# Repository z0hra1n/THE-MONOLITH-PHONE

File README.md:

# MONOLITH

Ahh, i finally get to yap about it.
This is MONOLITH. a phone, a brick , a portable computer, but most importantly, a MONOLITH.
The reason im calling it a monolith cuz its literally gonna be built like a shiny MONOLITH. especially because its outer body is inteded to be made from aluminum which acts as a passive heat sink and looks pretty cool.The design was heavily inspired by Nothing and Apple.

The pcb is quite complicated, and the design is pretty human.It was not easy to make as i am only 15, this is my second pcb, the schematic itself was very hard.The pcb ws harder.I got help from reddit and tomachie.com with the schematic so it was pretty easy to disagnose.But, when it came to me m,aking the pcb, after i was done connecting everything, the drc gave 2000 violations.I was scared, but turns out most of those were easy fixable in one or two clicks.I also did not keep in mind the manufacturing constraints, so i fixed the values, and most of the errors were gone.I was pleased.

Finally, i made the enclosure very minimalist and functional.The back has a plastic went to let out the rf and wifi/bt signals.
the rear camera physically rotates to become the selfie camera.

The specs are pretty nuts.It has the radxa nx5 16 gb ram and 256 emms variant.An oled with 120hz refresh rate, and a batter of about 120000 mah.Im not sure itll last much without optimisation tho.

Yeah! i hope it overtakes apple!

| Purpose | Component / Item | Qty | Cost (USD) | Distributor | Part Number |
|---------|-------------------|----:|-----------:|------------|-------------|
| Decoupling | 10µF 25V X5R 0603 Capacitor | 10 | $1.46 | Digi-Key | GRM188R61E106MA73J |
| Bulk Decoupling | 22µF 16V 0603 Capacitor | 12 | $4.44 | Digi-Key | GMC10X5R226M16NTCT |
| Power Filtering | 1µF 25V X7R 0603 Capacitor | 10 | $0.52 | Digi-Key | TMK107B7105KA-T |
| Signal Filtering | 10nF 100V X7R Capacitor | 5 | $0.48 | Digi-Key | GCM188R72A103KA37D |
| Signal Filtering | 47nF 50V X7R Capacitor | 5 | $1.00 | Digi-Key | GCM188R71H473KA55D |
| Decoupling | 100nF 50V Y5V Capacitor | 5 | $0.48 | Digi-Key | CC0603ZRY5V9BB104 |
| Crystal Load | 18pF C0G Capacitor | 5 | $1.29 | Digi-Key | QSCP251Q180J1GV001T |
| Power Filtering | 4.7µF 25V X5R Capacitor | 5 | $1.15 | Digi-Key | GRM188R61E475KE11D |
| Pull-ups / General | 10kΩ 1% Resistor | 15 | $0.46 | Digi-Key | CRCW060310K0FKEA |
| Voltage Divider | 47kΩ 1% Resistor | 5 | $0.48 | Digi-Key | RC0603FR-0747KL |
| Feedback Divider | 255kΩ 1% Resistor | 5 | $0.48 | Digi-Key | ERJ-3EKF2553V |
| Feedback Divider | 180kΩ 5% Resistor | 5 | $0.48 | Digi-Key | RC0603JR-07180KL |
| Feedback Divider | 56kΩ 1% Resistor | 5 | $0.48 | Digi-Key | ERJ-3EKF5602V |
| Pull-ups | 2.2kΩ 1% Resistor | 10 | $0.24 | Digi-Key | RC0603FR-072K2L |
| USB Configuration | 5.1kΩ 1% Resistor | 5 | $0.53 | Digi-Key | RC0603FR-075K1L |
| Precision Divider | 29.8kΩ 0.1% Resistor | 5 | $0.53 | Digi-Key | RT0603BRD0729K8L |
| General Purpose | 12kΩ 1% Resistor | 5 | $0.48 | Digi-Key | RC0603FR-0712KL |
| Feedback Divider | 240kΩ 5% Resistor | 5 | $0.48 | Digi-Key | ERJ-3GEYJ244V |
| General Purpose | 1kΩ 1% Resistor | 5 | $0.48 | Digi-Key | CRCW06031K00FKEA |
| Compute Module Interface | 260-pin SODIMM Socket | 2 | $3.50 | Digi-Key | 2309407-1 |
| Display Interface | 22-pin FFC Connector | 2 | $4.91 | Digi-Key | FH12-22S-0.5SH(55) |
| Display Output | Micro HDMI Receptacle | 2 | $3.94 | Digi-Key | 0467651301 |
| USB Connectivity | USB Type-C Receptacle | 2 | $0.61 | Digi-Key | USB4970-00-A |
| Battery Charging | BQ25895 Li-Ion Charger IC | 2 | $6.42 | Digi-Key | BQ25895RTWR |
| Audio Output | SSM2518 Class-D Amplifier | 1 | $7.18 | Digi-Key | SSM2518CPZ |
| Input Protection | 6V TVS Diode | 2 | $0.92 | Digi-Key | SMAJ6.0CA |
| 5V Power Rail | TPS61088 10A Boost Converter | 2 | $5.24 | Digi-Key | TPS61088RHLR |
| USB Protection | USB ESD Protection IC | 5 | $5.64 | Digi-Key | TPD2EUSB30DRTR |
| RF Connection | U.FL (MHF1) Coax Cable | 1 | $2.04 | Digi-Key | CA-DKCA1-100L1-I0I0 |
| USB Expansion | USB2512B 2-Port USB Hub | 2 | $3.36 | Digi-Key | USB2512B-AEZG |
| Motion Sensing | BMI270 IMU | 1 | $4.04 | Digi-Key | BMI270 |
| Clock Source | 24MHz Crystal | 2 | $0.99 | Digi-Key | 535-10643-1 |
| User Input | Tactile Push Button | 5 | $1.82 | Digi-Key | SWT0005-015516SSAC |
| Power Stage | 2.2µH 15A Inductor | 2 | $2.81 | Digi-Key | MWSA1205S-2R2MT |
| Power Stage | 1µH 10A Inductor | 2 | $4.41 | Digi-Key | 74437349010 |
| 1.8V Rail | AP2112K 1.8V LDO | 2 | $0.52 | Digi-Key | AP2112K-1.8TRG1 |
| 3.3V Rail | TLV75533 3.3V LDO | 2 | $0.59 | Digi-Key | TLV75533PDQNR |
| Cellular Connectivity | LTE FPC Antenna | 1 | $2.81 | Digi-Key | AANI-FB-0173 |
| Display Cable | Micro HDMI to Mini HDMI Cable | 1 | $4.68 | Digi-Key | FIT0649 |
| USB Accessories | USB-A to Micro USB Cable | 2 | $3.02 | Digi-Key | DH-20M50055 |
| USB Accessories | USB-C to USB-C Cable | 1 | $4.46 | Digi-Key | 10165794-Z0100YBLF |
| Additional Decoupling | 100nF X7R Capacitor | 10 | $0.67 | Digi-Key | C0603C104K3RACTU |
| Thermal Management | Heat Sink Thermal Sticker | 1 | $1.43 | Digi-Key | 6308 |
| Assembly | Kapton Tape (10mm) | 1 | $2.78 | Digi-Key | KAPTON-TAPE10MM |
| Temperature Monitoring | 10kΩ NTC Thermistor | 2 | $1.88 | Digi-Key | B57861S0103F040 |
| Camera | 12MP IMX477P Camera Module | 1 | $59.99 | Arducam | B0517 |
| Miscellaneous | Batteries, BLE Module, Connectors | 4 | $290.47 | AliExpress | Various |
| PCB Manufacturing | PCB Fabrication + Engineering | 1 | $72.96 | PCB Fab | — |
| Portable Power | 20,000mAh Power Bank | 1 | $30.29 | Amazon | Duracell |
| Enclosure | CNC Aluminium Enclosure (Estimate) | 1 | $100.00 | Local Fabricator | — |
| **TOTAL** | | | **$649.81** | | |

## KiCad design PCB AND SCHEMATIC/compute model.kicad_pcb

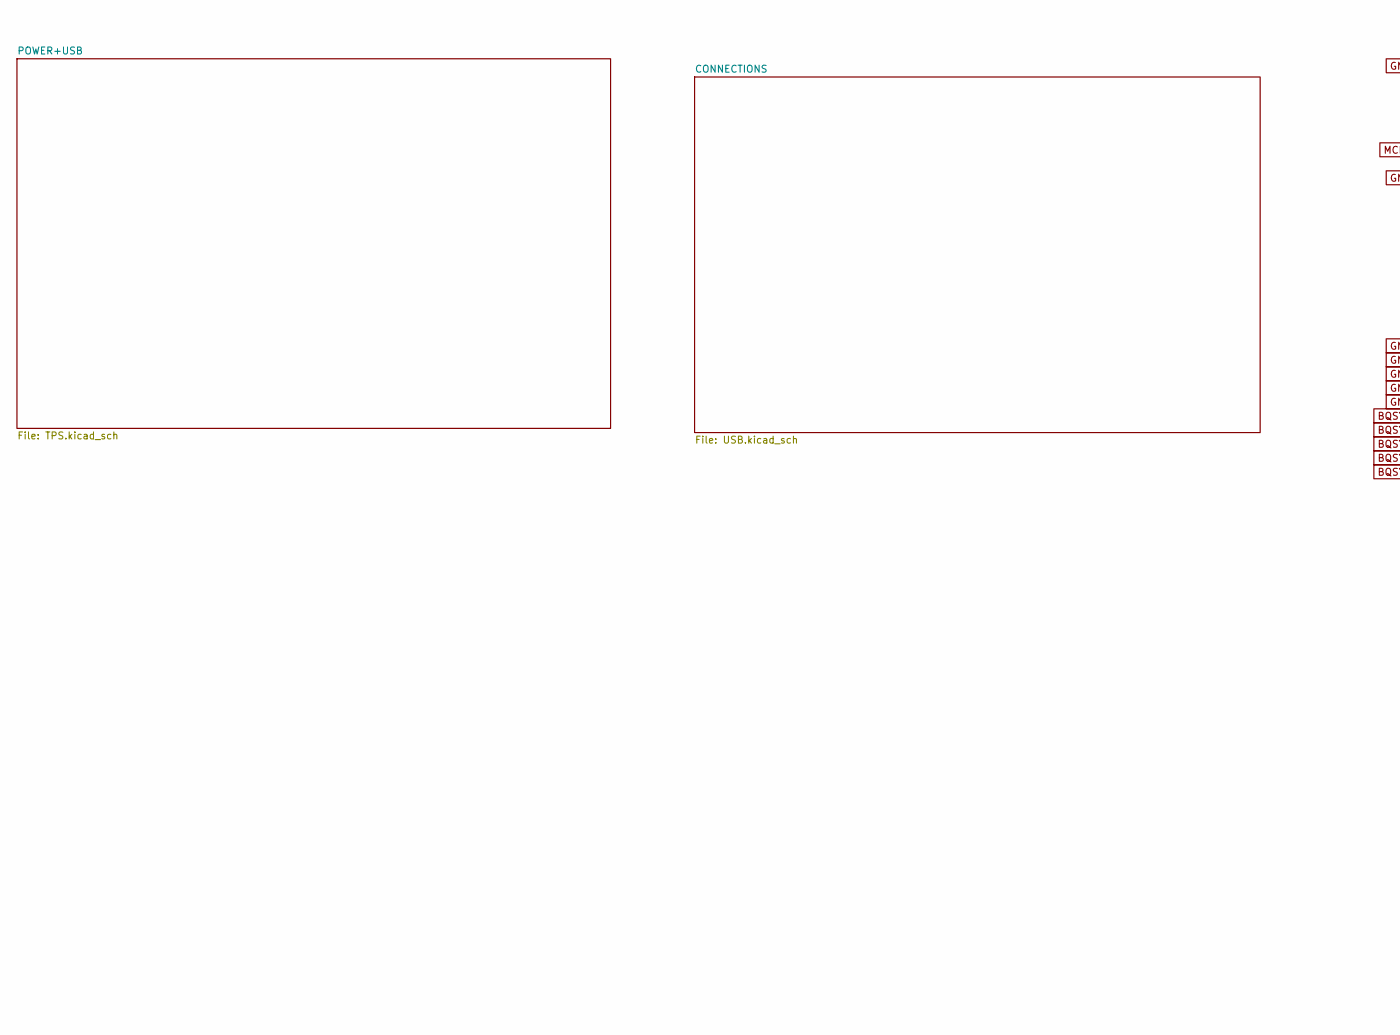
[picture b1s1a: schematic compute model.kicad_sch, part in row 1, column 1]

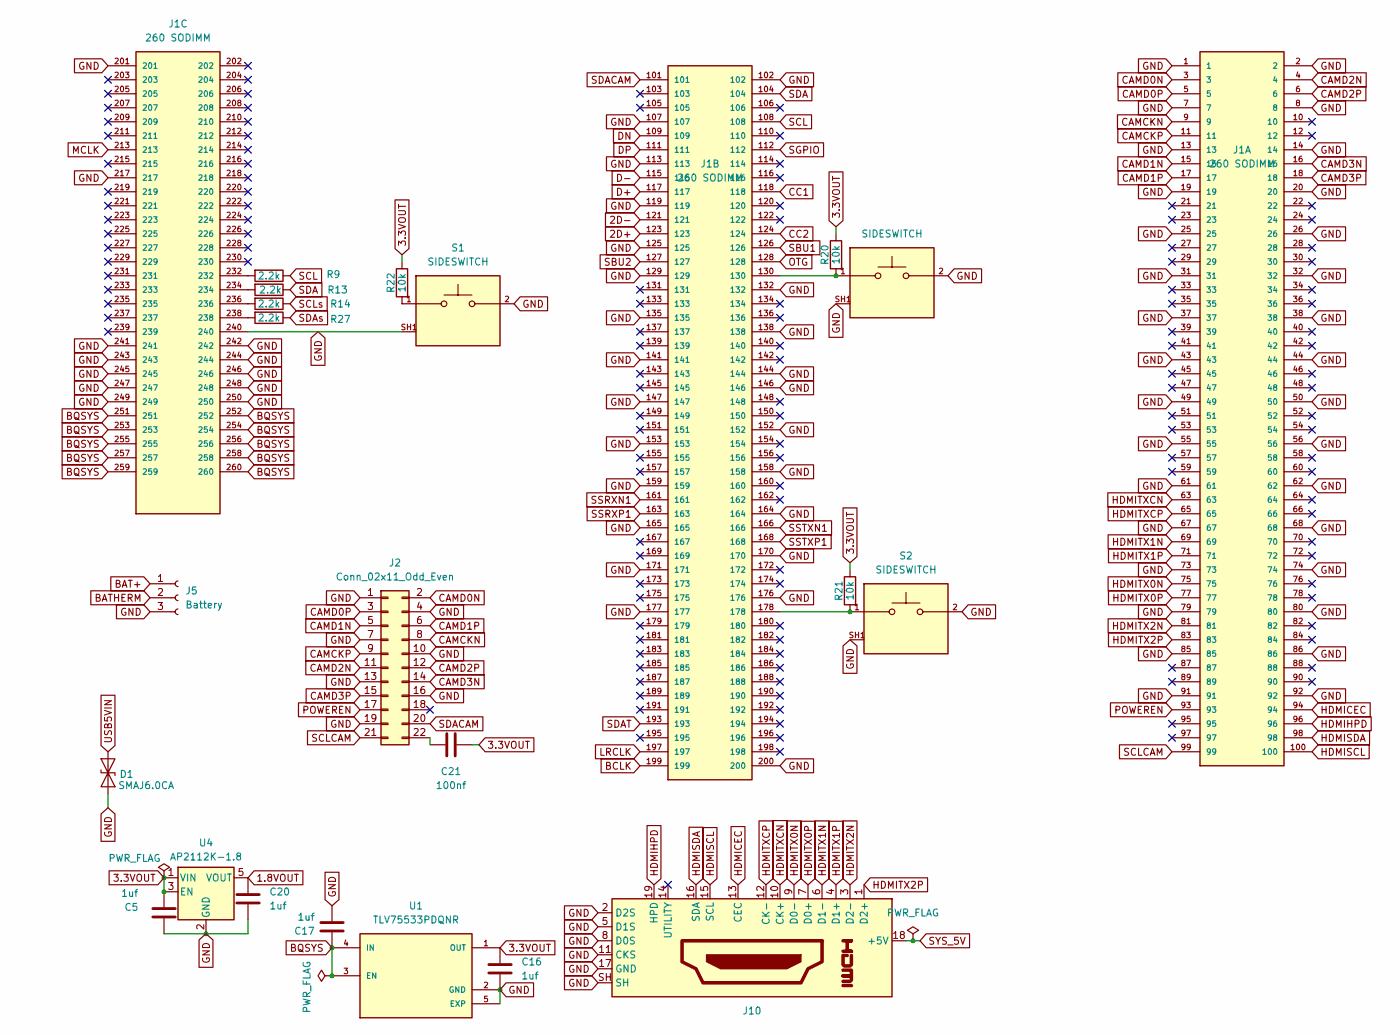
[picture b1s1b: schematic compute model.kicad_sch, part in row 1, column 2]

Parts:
C5, C16, C17, C20: 1uf; C_0603_1608Metric_Pad1.08x0.95mm_HandSolder
C21: 100nf; C_0603_1608Metric_Pad1.08x0.95mm_HandSolder
D1: SMAJ6.0CA; D_SMA_Handsoldering
J1: 260 SODIMM; 260; PARTREV 5
J2: Conn_02x11_Odd_Even; Hirose_FH12-22S-0.5SH_1x22-1MP_P0.50mm_Horizontal
J5: Battery; battery
J10: HDMI_A; HDMI_Micro-D_Molex_46765-2xxx
R9, R13, R14, R27: 2.2k; R_0603_1608Metric_Pad0.98x0.95mm_HandSolder
R20, R21, R22: 10k; R_0603_1608Metric_Pad0.98x0.95mm_HandSolder
S1, S2, S3: SIDESWITCH
U1: TLV75533PDQNR; TLV
U4: AP2112K-1.8; SOT-23-5

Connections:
1.8VOUT: C20.1, U4.5 (VOUT); also elsewhere on the board
2D+: J1.123; also elsewhere on the board
2D-: J1.121; also elsewhere on the board
3.3VOUT: C5.2, C16.1, C21.1, R20.1, R21.1, R22.1, U1.1 (OUT), U4.1 (VIN), U4.3 (EN); also elsewhere on the board
BAT+: J5.1; also elsewhere on the board
BATHERM: J5.2; also elsewhere on the board
BCLK: J1.199; also elsewhere on the board
BQSYS: C17.1, J1.251, J1.252, J1.253, J1.254, J1.255, J1.256, J1.257, J1.258, J1.259, J1.260, U1.3 (EN), U1.4 (IN); also elsewhere on the board
CAMCKN: J1.9, J2.8
CAMCKP: J1.11, J2.9
CAMD0N: J1.3, J2.2
CAMD0P: J1.5, J2.3
CAMD1N: J1.15, J2.5
CAMD1P: J1.17, J2.6
CAMD2N: J1.4, J2.11
CAMD2P: J1.6, J2.12
CAMD3N: J1.16, J2.14
CAMD3P: J1.18, J2.15
CC1: J1.118; also elsewhere on the board
CC2: J1.124; also elsewhere on the board
D+: J1.117; also elsewhere on the board
D-: J1.115; also elsewhere on the board
DN: J1.109; also elsewhere on the board
DP: J1.111; also elsewhere on the board
GND: C5.1, C16.2, C17.2, C20.2, D1.1 (A1), J1.1, J1.2, J1.7, J1.8, J1.13, J1.14, J1.19, J1.20, J1.25, J1.26, J1.31, J1.32, J1.37, J1.38, J1.43, J1.44, J1.49, J1.50, J1.55, J1.56, J1.61, J1.62, J1.67, J1.68, J1.73, J1.74, J1.79, J1.80, J1.85, J1.86, J1.91, J1.92, J1.102, J1.107, J1.113, J1.119, J1.125, J1.129, J1.132, J1.135, J1.138, J1.141, J1.144, J1.146, J1.147, J1.152, J1.153, J1.158, J1.159, J1.164, J1.165, J1.170, J1.171, J1.176, J1.177, J1.200, J1.201, J1.217, J1.240, J1.241, J1.242, J1.243, J1.244, J1.245, J1.246, J1.247, J1.248, J1.249, J1.250, J2.1, J2.4, J2.7, J2.10, J2.13, J2.16, J2.19, J5.3, J10.2 (D2S), J10.5 (D1S), J10.8 (D0S), J10.11 (CKS), J10.17 (GND), J10.SH, S1.2, S1.SH1, S2.2, S2.SH1, S3.2, S3.SH1, U1.2 (GND), U1.5 (EXP), U4.2 (GND); also elsewhere on the board
HDMICEC: J1.94, J10.13 (CEC)
HDMIHPD: J1.96, J10.19 (HPD)
HDMISCL: J1.100, J10.15 (SCL)
HDMISDA: J1.98, J10.16 (SDA)
HDMITX0N: J1.75, J10.9 (D0-)
HDMITX0P: J1.77, J10.7 (D0+)
HDMITX1N: J1.69, J10.6 (D1-)
HDMITX1P: J1.71, J10.4 (D1+)
HDMITX2N: J1.81, J10.3 (D2-)
HDMITX2P: J1.83, J10.1 (D2+)
HDMITXCN: J1.63, J10.10 (CK+)
HDMITXCP: J1.65, J10.12 (CK-)
LRCLK: J1.197; also elsewhere on the board
MCLK: J1.213; also elsewhere on the board
unnamed: J1.130, R20.2, S3.1
unnamed: J1.178, R21.2, S2.1
unnamed: J1.232, R9.2
unnamed: J1.234, R13.2
unnamed: J1.236, R14.2
unnamed: J1.238, R27.2
unnamed: C21.2, J2.22
unnamed: R22.2, S1.1
OTG: J1.128; also elsewhere on the board
POWEREN: J1.93, J2.17
SBU1: J1.126; also elsewhere on the board
SBU2: J1.127; also elsewhere on the board
SCL: J1.108, R9.1; also elsewhere on the board
SCLs: R14.1; also elsewhere on the board
SDA: J1.104, R13.1; also elsewhere on the board
SDAT: J1.193; also elsewhere on the board
SDAs: R27.1; also elsewhere on the board
SGPIO: J1.112; also elsewhere on the board
SSRXN1: J1.161; also elsewhere on the board
SSRXP1: J1.163; also elsewhere on the board
SSTXN1: J1.166; also elsewhere on the board
SSTXP1: J1.168; also elsewhere on the board
SYS_5V: J10.18 (+5V); also elsewhere on the board
USB5VIN: D1.2 (A2); also elsewhere on the board

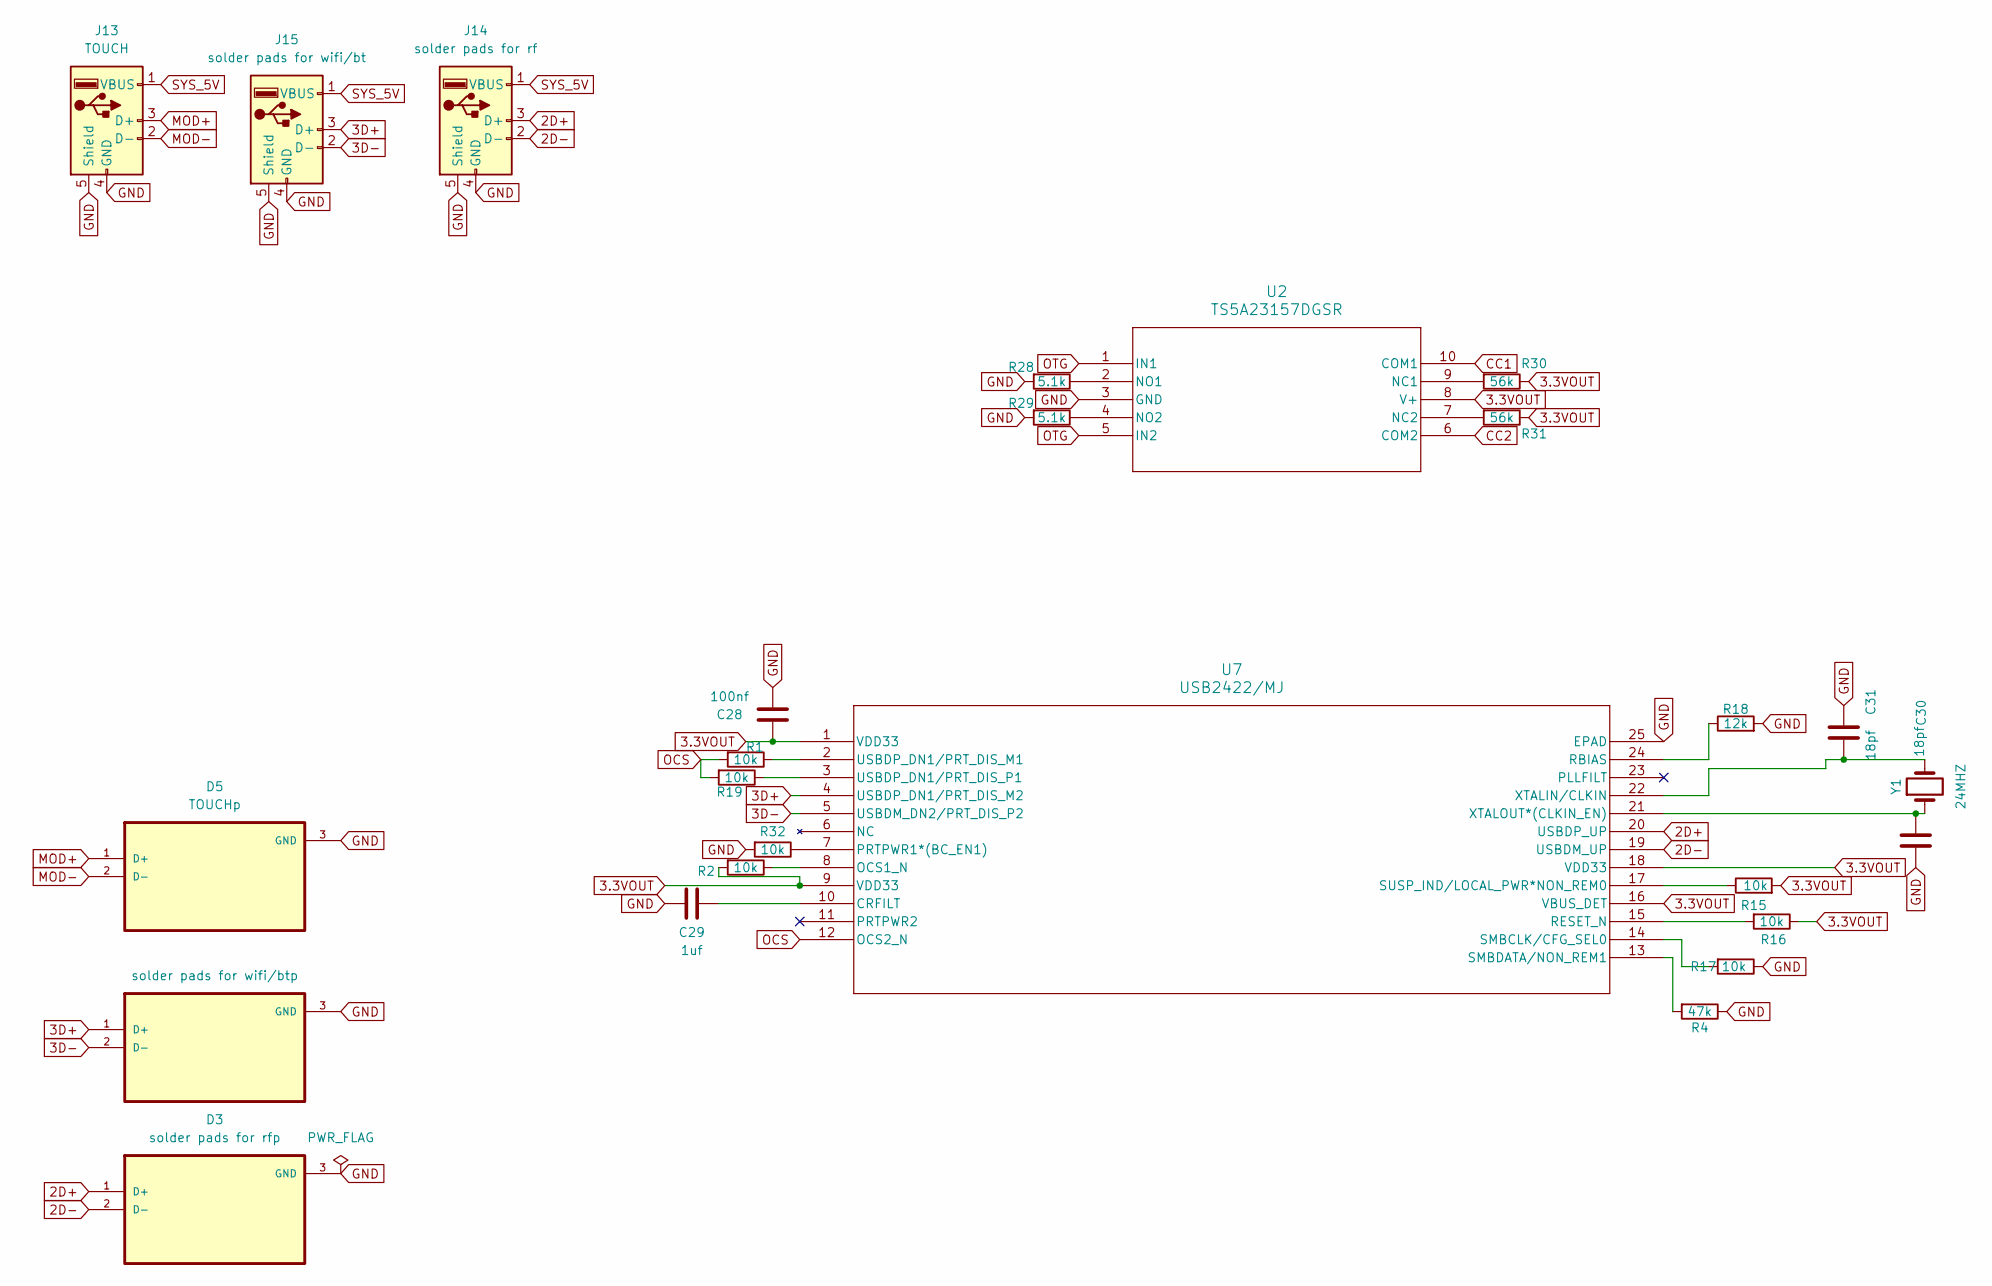
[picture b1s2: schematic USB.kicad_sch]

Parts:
C28: 100nf; C_0603_1608Metric_Pad1.08x0.95mm_HandSolder
C29: 1uf; C_0603_1608Metric_Pad1.08x0.95mm_HandSolder
C30, C31: 18pf; C_0603_1608Metric_Pad1.08x0.95mm_HandSolder
D3: solder pads for rfp; SOTFL35P100X50-3N; DigiKey_Part_Number 296-25509-1-ND
D4: solder pads for wifi/btp; SOTFL35P100X50-3N; DigiKey_Part_Number 296-25509-1-ND
D5: TOUCHp; SOTFL35P100X50-3N; DigiKey_Part_Number 296-25509-1-ND
J13: TOUCH
J14: solder pads for rf; RF
J15: solder pads for wifi/bt; WIFI_BT
R1, R2, R15, R16, R17, R19, R32: 10k; R_0603_1608Metric_Pad0.98x0.95mm_HandSolder
R4: 47k; R_0603_1608Metric_Pad0.98x0.95mm_HandSolder
R18: 12k; R_0603_1608Metric_Pad0.98x0.95mm_HandSolder
R28, R29: 5.1k; R_0603_1608Metric_Pad0.98x0.95mm_HandSolder
R30, R31: 56k; R_0603_1608Metric_Pad0.98x0.95mm_HandSolder
U2: TS5A23157DGSR; DGS10
U7: USB2422/MJ; HUB
Y1: 24MHZ; Crystal_SMD_5032-2Pin_5.0x3.2mm_HandSoldering

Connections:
2D+: D3.1 (D+), J14.3 (D+), U7.20 (USBDP_UP); also elsewhere on the board
2D-: D3.2 (D-), J14.2 (D-), U7.19 (USBDM_UP); also elsewhere on the board
3.3VOUT: C28.2, R2.2, R15.2, R16.1, R30.1, R31.1, U2.8 (V+), U7.1 (VDD33), U7.9 (VDD33), U7.16 (VBUS_DET), U7.18 (VDD33); also elsewhere on the board
3D+: D4.1 (D+), J15.3 (D+), U7.4 (USBDP_DN1/PRT_DIS_M2)
3D-: D4.2 (D-), J15.2 (D-), U7.5 (USBDM_DN2/PRT_DIS_P2)
CC1: U2.10 (COM1); also elsewhere on the board
CC2: U2.6 (COM2); also elsewhere on the board
GND: C28.1, C29.2, C30.2, C31.1, D3.3 (GND), D4.3 (GND), D5.3 (GND), J13.4 (GND), J13.5 (Shield), J14.4 (GND), J14.5 (Shield), J15.4 (GND), J15.5 (Shield), R4.1, R17.1, R18.2, R28.2, R29.2, R32.2, U2.3 (GND), U7.25 (EPAD); also elsewhere on the board
MOD+: D5.1 (D+), J13.3 (D+)
MOD-: D5.2 (D-), J13.2 (D-)
unnamed: R30.2, U2.9 (NC1)
unnamed: R31.2, U2.7 (NC2)
unnamed: R28.1, U2.2 (NO1)
unnamed: R29.1, U2.4 (NO2)
unnamed: C29.1, U7.10 (CRFILT)
unnamed: R2.1, U7.8 (OCS1_N)
unnamed: R32.1, U7.7 (PRTPWR1*(BC_EN1))
unnamed: R18.1, U7.24 (RBIAS)
unnamed: R16.2, U7.15 (RESET_N)
unnamed: R17.2, U7.14 (SMBCLK/CFG_SEL0)
unnamed: R4.2, U7.13 (SMBDATA/NON_REM1)
unnamed: R15.1, U7.17 (SUSP_IND/LOCAL_PWR*NON_REM0)
unnamed: R1.1, U7.2 (USBDP_DN1/PRT_DIS_M1)
unnamed: R19.1, U7.3 (USBDP_DN1/PRT_DIS_P1)
unnamed: C31.2, U7.22 (XTALIN/CLKIN), Y1.2
unnamed: C30.1, U7.21 (XTALOUT*(CLKIN_EN)), Y1.1
OCS: R1.2, R19.2, U7.12 (OCS2_N)
OTG: U2.1 (IN1), U2.5 (IN2); also elsewhere on the board
SYS_5V: J13.1 (VBUS), J14.1 (VBUS), J15.1 (VBUS); also elsewhere on the board

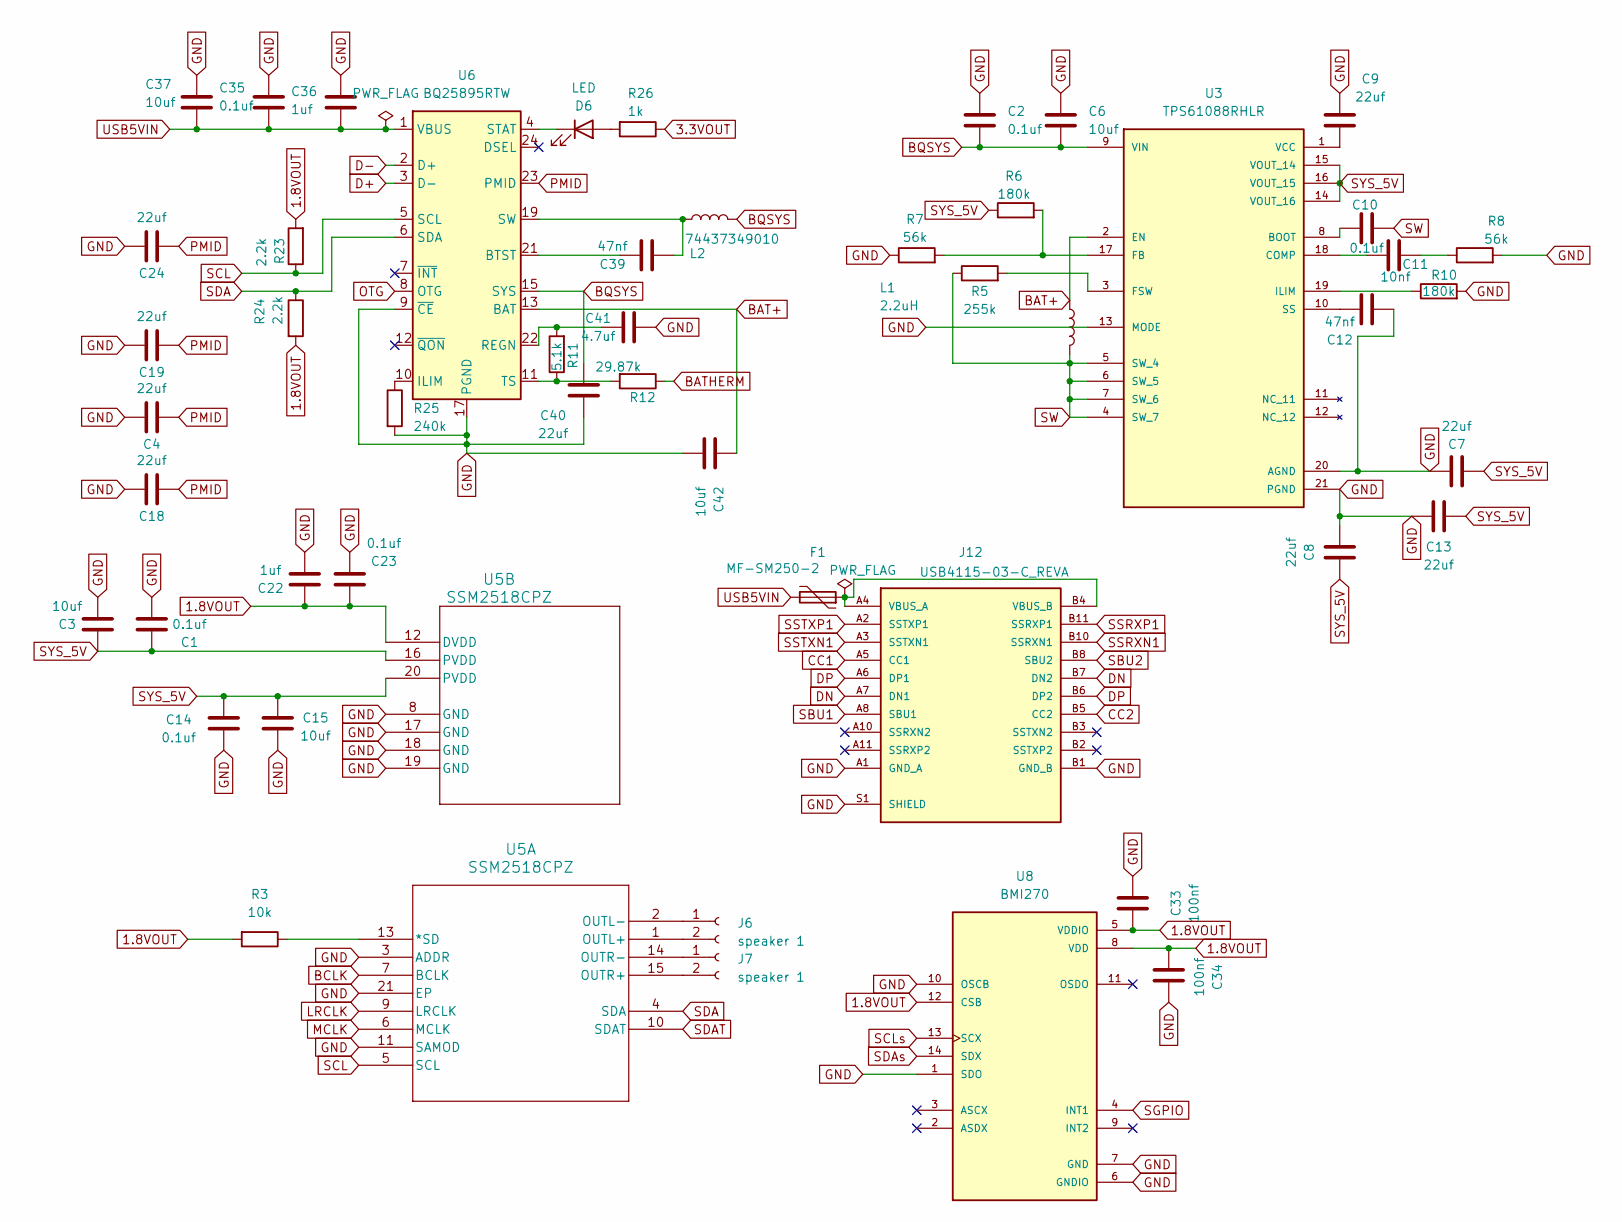
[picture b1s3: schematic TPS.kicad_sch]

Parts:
C1, C2, C10, C14, C23, C35: 0.1uf; C_0603_1608Metric_Pad1.08x0.95mm_HandSolder
C3, C6, C15, C37, C42: 10uf; C_0603_1608Metric_Pad1.08x0.95mm_HandSolder
C4, C7, C8, C9, C13, C18, C19, C24, C40: 22uf; C_0603_1608Metric_Pad1.08x0.95mm_HandSolder
C11: 10nf; C_0603_1608Metric_Pad1.08x0.95mm_HandSolder
C12, C39: 47nf; C_0603_1608Metric_Pad1.08x0.95mm_HandSolder
C22, C36: 1uf; C_0603_1608Metric_Pad1.08x0.95mm_HandSolder
C33, C34: 100nf; C_0603_1608Metric_Pad1.08x0.95mm_HandSolder
C41: 4.7uf; C_0603_1608Metric_Pad1.08x0.95mm_HandSolder
D6: LED; LED_0603_1608Metric_Pad1.05x0.95mm_HandSolder
F1: MF-SM250-2; FUSE_MF-SM185_BRN
J6, J7: speaker 1; JST_PH_S2B-PH-K_1x02_P2.00mm_Horizontal
J12: USB4115-03-C_REVA; USB 3.0; PARTREV A
L1: 2.2uH; INDUCTOR
L2: 74437349010; D_SOD-323
R3: 10k; R_0603_1608Metric_Pad0.98x0.95mm_HandSolder
R5: 255k; R_0603_1608Metric_Pad0.98x0.95mm_HandSolder
R6, R10: 180k; R_0603_1608Metric_Pad0.98x0.95mm_HandSolder
R7, R8: 56k; R_0603_1608Metric_Pad0.98x0.95mm_HandSolder
R11: 5.1k; R_0603_1608Metric_Pad0.98x0.95mm_HandSolder
R12: 29.87k; R_0603_1608Metric_Pad0.98x0.95mm_HandSolder
R23, R24: 2.2k; R_0603_1608Metric_Pad0.98x0.95mm_HandSolder
R25: 240k; R_0603_1608Metric_Pad0.98x0.95mm_HandSolder
R26: 1k; R_0603_1608Metric_Pad0.98x0.95mm_HandSolder
U3: TPS61088RHLR; TPS
U5: SSM2518CPZ; SSM
U6: BQ25895RTW; Texas_RTW_WQFN-24-1EP_4x4mm_P0.5mm_EP2.7x2.7mm_ThermalVias
U8: BMI270; BMI; DigiKey_Part_Number 828-1091-1-ND

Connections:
1.8VOUT: C22.2, C23.2, C33.2, C34.2, R3.2, R23.2, R24.2, U5.12 (DVDD), U8.5 (VDDIO), U8.8 (VDD), U8.12 (CSB); also elsewhere on the board
3.3VOUT: R26.1; also elsewhere on the board
BAT+: C42.1, L1.1, U3.2 (EN), U6.13 (BAT), U6.14 (BAT); also elsewhere on the board
BATHERM: R12.1; also elsewhere on the board
BCLK: U5.7 (BCLK); also elsewhere on the board
BQSYS: C2.2, C6.2, C40.2, L2.2, U3.9 (VIN), U6.15 (SYS), U6.16 (SYS); also elsewhere on the board
CC1: J12.A5 (CC1); also elsewhere on the board
CC2: J12.B5 (CC2); also elsewhere on the board
D+: U6.3 (D-); also elsewhere on the board
D-: U6.2 (D+); also elsewhere on the board
DN: J12.A7 (DN1), J12.B7 (DN2); also elsewhere on the board
DP: J12.A6 (DP1), J12.B6 (DP2); also elsewhere on the board
GND: C1.1, C2.1, C3.1, C4.2, C6.1, C7.1, C8.2, C9.2, C12.2, C13.2, C14.1, C15.1, C18.2, C19.2, C22.1, C23.1, C24.2, C33.1, C34.1, C35.1, C36.1, C37.1, C40.1, C41.2, C42.2, J12.A1 (GND_A), J12.B1 (GND_B), J12.S1 (SHIELD), R7.1, R8.2, R10.2, R25.2, U3.13 (MODE), U3.20 (AGND), U3.21 (PGND), U3.23, U3.24, U3.25, U3.26, U3.27, U3.28, U3.29, U3.gnd, U5.3 (ADDR), U5.8 (GND), U5.11 (SAMOD), U5.17 (GND), U5.18 (GND), U5.19 (GND), U5.21 (EP), U6.9 (~CE), U6.17 (PGND), U6.18 (PGND), U6.25 (PGND), U8.1 (SDO), U8.6 (GNDIO), U8.7 (GND), U8.10 (OSCB); also elsewhere on the board
LRCLK: U5.9 (LRCLK); also elsewhere on the board
MCLK: U5.6 (MCLK); also elsewhere on the board
unnamed: C11.2, R8.1
unnamed: C39.1, L2.1, U6.19 (SW), U6.20 (SW)
unnamed: D6.2 (A), R26.2
unnamed: D6.1 (K), U6.4 (STAT)
unnamed: J6.1, U5.2 (OUTL-)
unnamed: J6.2, U5.1 (OUTL+)
unnamed: J7.1, U5.14 (OUTR-)
unnamed: J7.2, U5.15 (OUTR+)
unnamed: F1.1, J12.A4 (VBUS_A), J12.B4 (VBUS_B)
unnamed: C10.1, U3.8 (BOOT)
unnamed: C11.1, U3.18 (COMP)
unnamed: R6.2, R7.2, U3.17 (FB)
unnamed: R5.2, U3.3 (FSW)
unnamed: R10.1, U3.19 (ILIM)
unnamed: C12.1, U3.10 (SS)
unnamed: C9.1, U3.1 (VCC)
unnamed: R3.1, U5.13 (*SD)
unnamed: C39.2, U6.21 (BTST)
unnamed: R25.1, U6.10 (ILIM)
unnamed: C41.1, R11.2, U6.22 (REGN)
unnamed: R11.1, R12.2, U6.11 (TS)
OTG: U6.8 (OTG); also elsewhere on the board
PMID: C4.1, C18.1, C19.1, C24.1, U6.23 (PMID)
SBU1: J12.A8 (SBU1); also elsewhere on the board
SBU2: J12.B8 (SBU2); also elsewhere on the board
SCL: R23.1, U5.5 (SCL), U6.5 (SCL); also elsewhere on the board
SCLs: U8.13 (SCX); also elsewhere on the board
SDA: R24.1, U5.4 (SDA), U6.6 (SDA); also elsewhere on the board
SDAT: U5.10 (SDAT); also elsewhere on the board
SDAs: U8.14 (SDX); also elsewhere on the board
SGPIO: U8.4 (INT1); also elsewhere on the board
SSRXN1: J12.B10 (SSRXN1); also elsewhere on the board
SSRXP1: J12.B11 (SSRXP1); also elsewhere on the board
SSTXN1: J12.A3 (SSTXN1); also elsewhere on the board
SSTXP1: J12.A2 (SSTXP1); also elsewhere on the board
SW: C10.2, L1.2, R5.1, U3.4 (SW_7), U3.5 (SW_4), U3.6 (SW_5), U3.7 (SW_6)
SYS_5V: C1.2, C3.2, C7.2, C8.1, C13.1, C14.2, C15.2, R6.1, U3.14 (VOUT_16), U3.15 (VOUT_14), U3.16 (VOUT_15), U5.16 (PVDD), U5.20 (PVDD); also elsewhere on the board
USB5VIN: C35.2, C36.2, C37.2, F1.2, U6.1 (VBUS); also elsewhere on the board

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
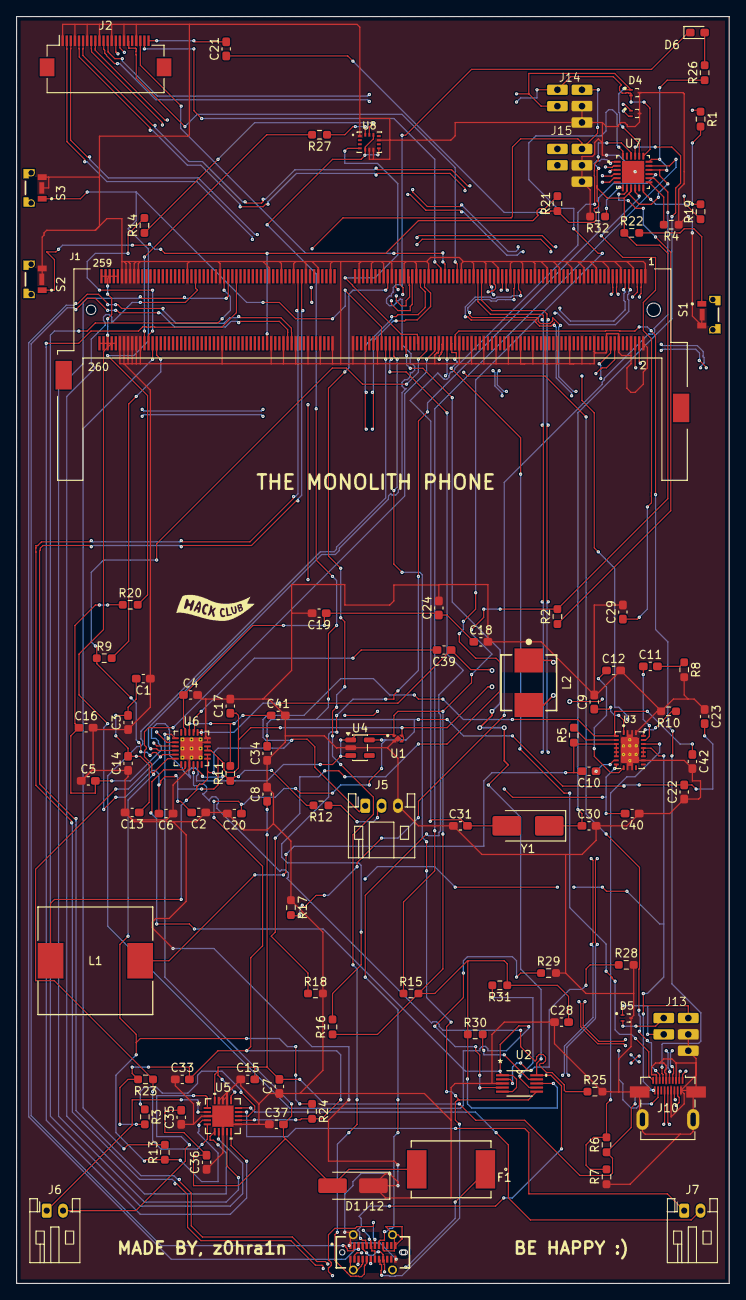
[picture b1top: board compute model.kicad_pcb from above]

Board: 4 copper layers, 87.1 x 154.9 mm, 99 parts (0 on the bottom side), 109 nets.

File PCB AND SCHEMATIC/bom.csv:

Designator,Footprint,Quantity,Value,LCSC Part #
"C1, C10, C14, C2, C23, C35",0603,6,0.1uf,
C11,0603,1,10nf,
"C12, C39",0603,2,47nf,
"C13, C18, C19, C24, C4, C40, C7, C8, C9",0603,9,22uf,
"C15, C3, C37, C42, C6",0603,5,10uf,
"C16, C17, C20, C22, C29, C36, C5",0603,7,1uf,
"C21, C28, C33, C34",0603,4,100nf,
"C30, C31",0603,2,18pf,
C41,0603,1,4.7uf,
D1,D_SMA_Handsoldering,1,SMAJ6.0CA,
D3,SOTFL35P100X50-3N,1,solder pads for rfp,
D4,SOTFL35P100X50-3N,1,solder pads for wifi/btp,
D5,SOTFL35P100X50-3N,1,TOUCHp,
D6,0603,1,LED,
F1,FUSE_MF-SM185_BRN,1,MF-SM250-2,
J1,260,1,260 SODIMM,
J10,HDMI_Micro-D_Molex_46765-2xxx,1,HDMI_A,
J12,USB 3.0,1,USB4115-03-C_REVA,
J13,TOUCH,1,TOUCH,
J14,RF,1,solder pads for rf,
J15,WIFI_BT,1,solder pads for wifi/bt,
J2,Hirose_FH12-22S-0.5SH_1x22-1MP_P0.50mm_Horizontal,1,Conn_02x11_Odd_Even,
J5,battery,1,Battery,
"J6, J7",JST_PH_S2B-PH-K_1x02_P2.00mm_Horizontal,2,speaker 1,
L1,INDUCTOR,1,2.2uH,
L2,WE-LHMI_7050,1,74437349010,
"R1, R15, R16, R17, R19, R2, R20, R21, R22, R3, R32",0603,11,10k,
"R10, R6",0603,2,180k,
"R11, R28, R29",0603,3,5.1k,
R12,0603,1,29.87k,
"R13, R14, R23, R24, R27, R9",0603,6,2.2k,
R18,0603,1,12k,
R25,0603,1,240k,
R26,0603,1,1k,
"R30, R31, R7, R8",0603,4,56k,
R4,0603,1,47k,
R5,0603,1,255k,
"S1, S2, S3",SIDESWITCH,3,SIDESWITCH,
U1,TLV,1,TLV75533PDQNR,
U2,DGS10,1,TS5A23157DGSR,
U3,TPS,1,TPS61088RHLR,
U4,SOT-23-5,1,AP2112K-1.8,
U5,SSM,1,SSM2518CPZ,
U6,Texas_RTW_WQFN-24-1EP_4x4mm_P0.5mm_EP2.7x2.7mm_ThermalVias,1,BQ25895RTW,
U7,HUB,1,USB2422/MJ,
U8,BMI,1,BMI270,
Y1,Crystal_SMD_5032-2Pin_5.0x3.2mm_HandSoldering,1,24MHZ,
